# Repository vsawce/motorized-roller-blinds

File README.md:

# Motorized Roller Blinds
A Raspberry Pi Pico W RP2040-based smart blinds project for my apartment.

I made this for fun as well as to minimize nocturnal light bleed from my apartment's outdoor lights while allowing myself to wake up to sunlight in the morning.

This system integrates with Home Assistant and MQTT, so a dedicated Home Assistant instance with the MQTT add-on is needed

## Build / Upload Instructions
As of this markdown's commit 
### Linux
1. Clone the [pico-sdk](https://github.com/raspberrypi/pico-sdk) and [FreeRTOS-Kernel](https://github.com/FreeRTOS/FreeRTOS-Kernel) repos
    * Follow their instructions for setup
2. If not done already, create the following system variables and assign them to pico-sdk and FreeRTOS-Kernel paths
    * Example in `~/.bashrc`:
      ```
      #PI PICO SDK
      export PICO_SDK_PATH=/home/<user>/pico-sdk/
      export FREERTOS_KERNEL_PATH=/home/<user>/FreeRTOS-Kernel/
      ```
    * `source ~/.bashrc` after
3. Clone this repo
4. `cd` into this repo's root directory
5. `mkdir build`
6. `cd build`
7. Run cmake in this directory
    * **Required options/arguments**:
      * `-DPICO_BOARD=pico_w`
      * `-DWIFI_SSID="<your_wifi_ssid>"`
      * `-DWIFI_PASSWORD="<your_wifi_pass>"`
      * `-DMQTT_CLIENT_ID="<custom_client_id>"`
        * Should be a custom and unique ID for each Pico W device. You choose.
      * `-DMQTT_USER=<"home_assistant_user">`
        * Should be the helper user you created specifically Home Assistant for MQTT
      * `-DMQTT_PASSWORD=<"home_assistant_pass">`
        * Should be the helper user's password you created specifically Home Assistant for MQTT
    * Example call: `cmake -DPICO_BOARD=pico_w -DWIFI_SSID="eduroam" -DWIFI_PASSWORD="abc123" -DMQTT_CLIENT_ID="picow_0" -DMQTT_USER="mqtt_test" -DMQTT_PASSWORD="xyz123" ..`
8. **Ensure the following user-defined macros in the program are correct**
    * definitions.h:
      * In `namespace BLINDS`, make sure your window height and blinds' shaft diameter is set accurately
      * In `namespace PIN`, make sure GPIO pins are set properly
    * wifi.h (may move these to definitions.h in the future):
      * `MQTT_ADDR` - point to the IP your Home Assistant is running on
      * `MQTT_ADDR_PORT` - point to the port your Home Assistant is configured to for MQTT
      * `MQTT_POS_REQUEST_TOPIC` - if you want to set a custom MQTT topic for position request (I use `/blinds/<MQTT_CLIENT_ID>/pos_request`)
      * `MQTT_POS_JSON_KEY` - JSON key string for Home Assistant -> Pico W blinds % position command (My example json: `{"pos":"50%"}`)
9. `make main` to build once all variables are set
10. Copy `src/main.uf2` into your Pico W and start a serial terminal!

## Home Assistant Example Config
As of Home Assistant Core 2025.3.3 and Home Assistant Operating System 15.0 
</br>
* After installing MQTT add-on and creating a dedicated Home Assistant user for MQTT:
  * Settings->Devices & services->MQTT
  * Click the three dots next to the Mosquitto integration entry->Reconfigure
  * Ensure port is set correctly, and then add the dedicated MQTT Home Assistant user's credentials
  * Submit
* Use something like the Studio Code Server add-on to edit `/config/configuration.yaml` (my current config):
  * ```
    # Loads default set of integrations. Do not remove.
    default_config:
    
    # Load frontend themes from the themes folder
    frontend:
      themes: !include_dir_merge_named themes
    
    automation: !include automations.yaml
    script: !include scripts.yaml
    scene: !include scenes.yaml
    
    input_number:
      slider1:
        name: Bedroom Blinds
        initial: 0
        min: 0
        max: 100
        step: 5
    mqtt:
      - cover:
          name: Smart Blinds
          unique_id: smart__blinds
          command_topic: "/blinds/picow_0/command"
          position_topic: "/blinds/picow_0/pos_status"
          set_position_topic: "/blinds/picow_0/pos_req"
          payload_open: "100"
          payload_close: "0"
          position_open: 100
          position_closed: 0
    ```
* Set up an automation with similar YAML:
  * ```
    - id: <AUTO_ASSIGNED_BY_HOMEASSISTANT?>
    alias: Adjust Blinds Position
    description: ""
    triggers:
      - trigger: state
        entity_id: input_number.slider1
    conditions: []
    actions:
      - action: mqtt.publish
        data_template:
          qos: "0"
          topic: "/blinds/picow_0/pos_request"
          payload: "{\"pos\":\"{{ states('input_number.slider1') | int }}%\"}"
    mode: single
    ```

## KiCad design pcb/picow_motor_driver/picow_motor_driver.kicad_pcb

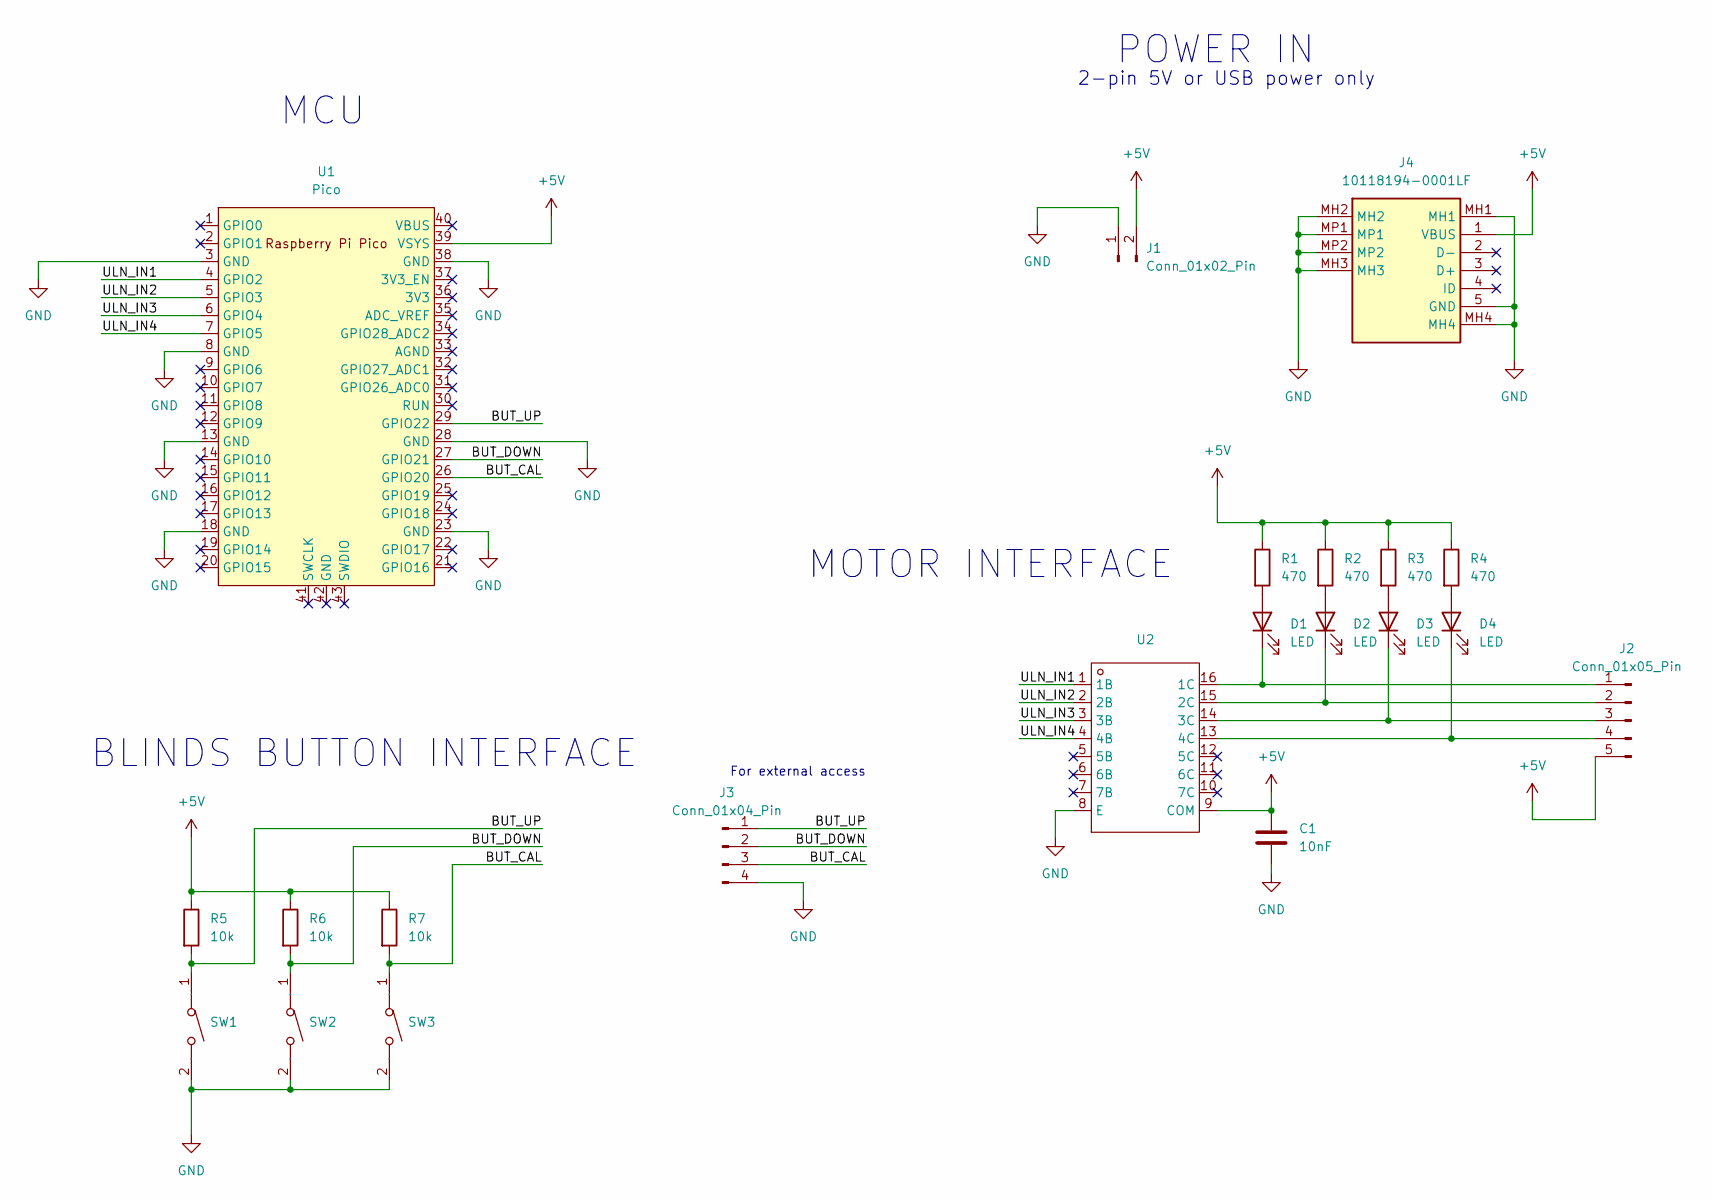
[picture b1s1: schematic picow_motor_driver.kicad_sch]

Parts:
C1: 10nF; C_0603_1608Metric
D1, D2, D3, D4: LED; LED_0603_1608Metric
J1: Conn_01x02_Pin; PinHeader_1x02_P2.54mm_Vertical
J2: Conn_01x05_Pin; S5B-XH-A
J3: Conn_01x04_Pin; S4BXHALFSN
J4: 10118194-0001LF; 101181940001LF; Manufacturer_Part_Number 10118194-0001LF
R1, R2, R3, R4: 470; R_0603_1608Metric
R5, R6, R7: 10k; R_0603_1608Metric
SW1, SW2, SW3: SW-SMD_L3.9-W3.0-P4.45; Manufacturer Part TS-1088-AR02016; LCSC Part Name 4*3*2mm 立贴 轻触开关
U1: Pico; RPi_Pico_SMD_TH
U2: SOIC-16_L9.9-W3.9-P1.27-LS6.0-BL; Manufacturer Part ULN2003D1013TR; LCSC Part Name ULN2003D1013TR

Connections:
+5V: C1.1, J1.2, J2.5, J4.1 (VBUS), R1.1, R2.1, R3.1, R4.1, R5.1, R6.1, R7.1, U1.39 (VSYS), U2.9 (COM)
/BUT_CAL: J3.3, R7.2, SW3.1, U1.26 (GPIO20)
/BUT_DOWN: J3.2, R6.2, SW2.1, U1.27 (GPIO21)
/BUT_UP: J3.1, R5.2, SW1.1, U1.29 (GPIO22)
/ULN_IN1: U1.4 (GPIO2), U2.1 (1B)
/ULN_IN2: U1.5 (GPIO3), U2.2 (2B)
/ULN_IN3: U1.6 (GPIO4), U2.3 (3B)
/ULN_IN4: U1.7 (GPIO5), U2.4 (4B)
GND: C1.2, J1.1, J3.4, J4.5 (GND), J4.MH1, J4.MH2, J4.MH3, J4.MH4, J4.MP1, J4.MP2, SW1.2, SW2.2, SW3.2, U1.3 (GND), U1.8 (GND), U1.13 (GND), U1.18 (GND), U1.23 (GND), U1.28 (GND), U1.38 (GND), U2.8 (E)
unnamed: D1.2 (A), R1.2
unnamed: D1.1 (K), J2.1, U2.16 (1C)
unnamed: D2.2 (A), R2.2
unnamed: D2.1 (K), J2.2, U2.15 (2C)
unnamed: D3.2 (A), R3.2
unnamed: D3.1 (K), J2.3, U2.14 (3C)
unnamed: D4.2 (A), R4.2
unnamed: D4.1 (K), J2.4, U2.13 (4C)

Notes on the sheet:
POWER IN
BLINDS BUTTON INTERFACE
2-pin 5V or USB power only
MCU
For external access
MOTOR INTERFACE

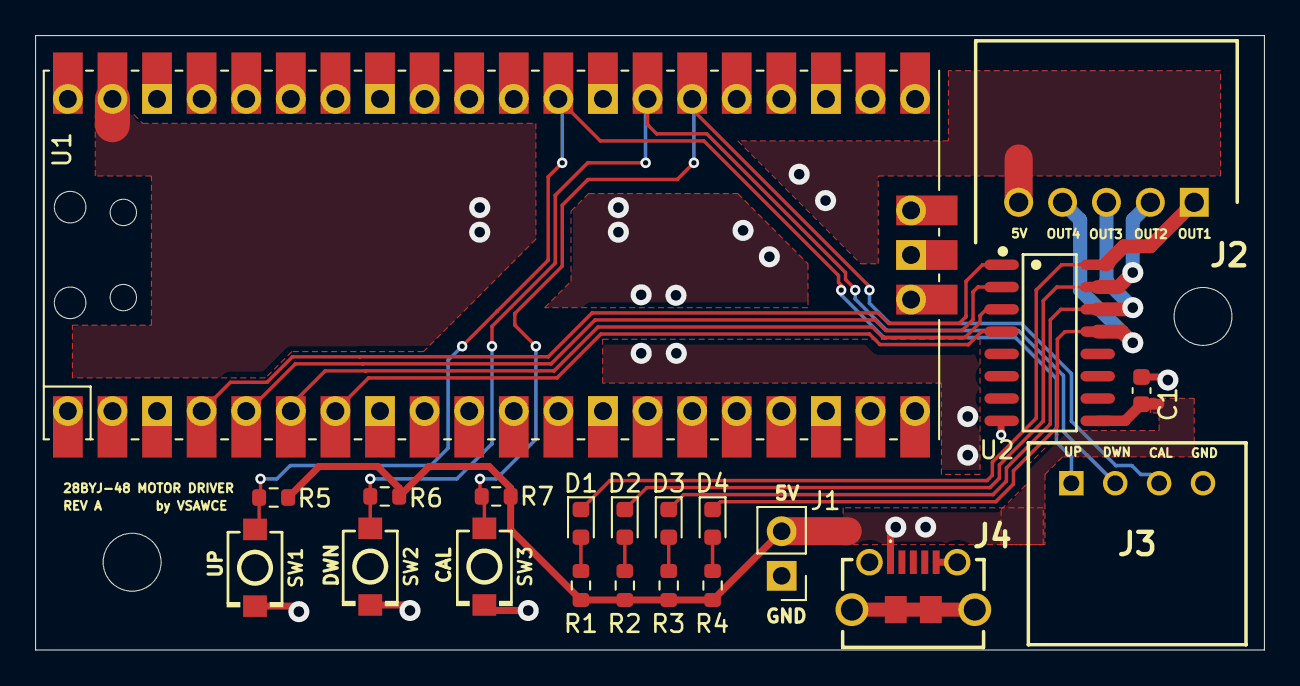
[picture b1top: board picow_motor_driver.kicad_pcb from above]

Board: 2 copper layers, 70.0 x 35.0 mm, 21 parts (0 on the bottom side), 17 nets.

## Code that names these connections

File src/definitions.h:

#ifndef DEFINITIONS_H
#define DEFINITIONS_H

#include "pico/stdlib.h"

//////////////////////////
//  CYW43 PARAMETERS    //
//////////////////////////

namespace CYW43
{
    constexpr int WIFI_TIMEOUT_MS = 30000; //30s timeout
}

//////////////////////////
//  BLIND PARAMETERS    //
/////////////////////////

namespace BLINDS
{
    constexpr uint8_t SHAFT_DIAMETER_MM = 40;               // ~4cm shaft
    constexpr uint16_t WINDOW_HEIGHT_MM = 1778 + 120;       // 70 inch window (1778mm) + ~5 in buffer
}

//////////////
//  PINS    //
//////////////

namespace PIN
{ 
    // constexpr for compile-time evalutation (modern C++?)
    constexpr uint8_t ULN2003_IN1   = 2;    //GPIO2
    constexpr uint8_t ULN2003_IN2   = 3;    //GPIO3
    constexpr uint8_t ULN2003_IN3   = 4;    //GPIO4
    constexpr uint8_t ULN2003_IN4   = 5;    //GPIO5

    constexpr uint8_t BUTTON_UP     = 22;   //GPIO22, move blinds up
    constexpr uint8_t BUTTON_DOWN   = 21;   //GPIO21, move blinds down
    constexpr uint8_t BUTTON_CALIB  = 20;   //GPIO20, calibrate blind position
}

namespace CYW43_PIN
{
    constexpr uint8_t LED = 0;
}



#endif

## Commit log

2024-09-13 Omitted build folder
2024-09-13 Hello world
2024-09-23 Added primary datasheets
2024-09-23 Enabled USB serial on hello_world
2024-09-25 Renamed hello_world C project into main CPP project
2024-09-27 Updated CMakeLists to glob all files in src/
2024-09-28 Added CYW43 wifi driver and updated CMakeList to accomodate
2024-09-28 Added modular topology to blink LED
2024-09-28 gitignore update to add .vscode
2024-12-04 Added motor and motor controller datasheet
2024-12-04 Added motor/motor controller pin definitions
2024-12-04 Added terribly crude but functioning motor proof-of-concept code
2024-12-04 Added discrete step update function
2024-12-04 Added drive mode select capability
2024-12-04 Added code to test one full shaft rotation
2024-12-09 Added reverse motor drive direction functionality
2025-01-12 #10: Reorganized CMake architecture a bit by adding subdirectory specific CMakeLists. Needs cleaning though
2025-01-13 #10: Fixed main's CMake structure so it compiles successfully and as intended
2025-01-13 #10: Removed old CMake architecture
2025-01-13 #7: Made LED blink in first step of RTOS conversion
2025-01-13 Added LED toggle macro in main function
2025-01-13 Minimally functional test code to blink LED while driving motor
2025-01-13 Cleaned up and organized main file comments
2025-01-15 #12: Added queue-based USB debug task prototype
2025-01-16 Commented out async context code out for now
2025-01-16 Adjusted task priority and stack size macros
2025-01-16 Slightly adjusted white-space and curly bracket formatting
2025-01-16 Added # of full shaft rotations function for RTOS
2025-01-17 #15: Added motor control based on # steps
2025-01-17 #15: Added motor control based on linear distance
2025-01-17 Added max height calculation directly to conditional
2025-01-17 Removed old blocking test functions for motor
2025-01-17 Eliminated infinite rotation in rotateNumFullRotations
2025-01-17 #2: Added var for current pos and calculation of steps based on window height
2025-01-17 Grab numeric limit based on numStepsToRotate's type rather than fixed uint32_t
2025-01-17 Added max/min retraction limits to rotateNumSteps
2025-01-17 Changed rotateNumFullRotations code to be a wrapper of rotateNumSteps
2025-01-17 #2: Added function skeleton rotateToPercent
2025-01-18 #2: Added rotateToPercent function to move to a percentage based on window height + some test code in motor_task
2025-01-18 Renamed init_wifi() to init()
2025-01-18 Removed __unused from blink_task params
2025-01-18 Commented out send_log calls
2025-01-18 #12: Migrated logging into own class and file
2025-01-18 Added getUptimeCentiseconds function
2025-01-18 Changed 100 to be constexpr var
2025-01-18 Corrected microseconds to centiseconds conversion
2025-01-18 Added printf style usage for Logger::send() and added timestamp prefix
2025-01-23 #11: Added ping dependencies
2025-01-23 #11: PING_ADDR macro
2025-01-23 Added basic code to connect to wifi
2025-01-23 #11: connectToWifi returns int instead of void
2025-01-23 #11: Panic/asserts during init - need to fix. Code broken
2025-01-27 #11: Fixed panic in NO_SYS=1 mode
2025-01-27 #11: Fixed panic in NO_SYS=0 mode
2025-01-27 Migrated contents of FreeRTOSConfig_examples_common.h to FreeRTOSConfig.h
2025-01-27 Feed Logger object into motor task struct instead of motor direction
2025-01-27 Added task start logging
2025-01-27 Removed unused motor direction var
2025-01-27 #11: Improved hard assert panic aversion on startup by moving motor and blink task creation to wifi_task but still needs fixing
2025-01-27 Added core # printout per task
2025-01-27 #11: Fixed assertion/panic issues for real? Moved logger task to initialize 2nd instead of first
2025-01-30 #11: Added IP printout
2025-02-04 Replaced hard-coded project name with
2025-02-04 Added current list directory
2025-02-04 Added LWIP_DEBUG and PING_DEBUG comments to compilation defs
2025-02-04 #11: Fixed ping.c include as this project is CPP
2025-02-12 #16: Added simple 5-second watchdog
2025-02-12 #3: Added button pin definitions
2025-02-12 #3: Added basic button GPIO interface for up, down, and calibration
2025-02-13 #18 & #3: Crude motor action based on button action
2025-02-25 #3: First rev of button-based manual motor control
2025-02-25 Added motor GPIO release function that can reduce idle power
2025-02-25 Moved repetitive cmd.pos assignment prior to conditionals
2025-02-25 #3, #4: Added calibration to 0 by button
2025-02-25 #17: Added lazy delay on calibration command to eliminate need for debouncing
2025-02-25 #20: Converted logger from C++ object/class to namespace-level/C style global functions
2025-02-25 #20: Adapter motor functions from printf to log_send
2025-02-25 #20: Cleaned up tasks after deletion of log object
2025-02-25 #8: Added log message differentiation as well as debug message enable/disable
2025-02-25 #20: Removed init.h and init.cpp, unnecessary
2025-02-28 #19: Used FreeRTOS timer to release motor x ms after motor command
2025-02-28 Added freertos ref manual in pdf
2025-03-13 MQTT related preprocessor macros and constants
2025-03-14 #21: Added MQTT broker connection and related infra
2025-03-17 #21: Basic subscribe code
2025-03-17 Removed unused internal wifi object
2025-03-17 #21: Removed test code in main
2025-03-17 #21: Added mqtt topic macro and changed topic
2025-03-17 #21: Added publish debug print
2025-03-19 #21: MQTT topic change
2025-03-19 #21: Proper string copying/handling for incoming MQTT data
2025-03-19 #21: MQTT position request macro rename
2025-03-19 Motor ptr passable into wifi class in order to add to queue
2025-03-19 #21: JSON percent parse function based on key template
2025-03-20 Increased log message max len from 64 to 128
2025-03-20 #21: Working debug code for custom simple json parser
2025-03-20 Removed unnecessary debug statements
2025-03-20 Connected wifi mqtt logic to motor and works. Let's goooooooooooooooo
2025-03-20 README build/config instructions
2025-05-06 Rev A of PCB
2025-05-07 Changed connectors out to JST, switched USB conn
2025-07-04 Swapped motor directions
2025-07-04 Window params
2025-07-04 Add limit bypass using buttons
2025-07-04 Motor drive speed params
2025-07-15 Adj params
2025-07-16 turn led off
2025-07-16 Fix timeout not being fed
2025-07-16 Increase log message size
2025-07-16 Improve wifi debug
2025-07-16 Turn back on LED as it breaks init
2025-07-17 Increase WDT by adding wifi timeout in ms
2025-08-02 Ignore build_pico2/
2025-08-02 Disable led
